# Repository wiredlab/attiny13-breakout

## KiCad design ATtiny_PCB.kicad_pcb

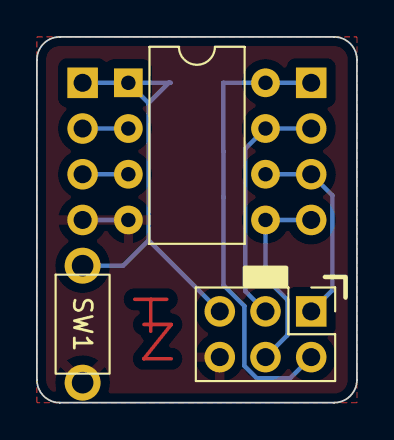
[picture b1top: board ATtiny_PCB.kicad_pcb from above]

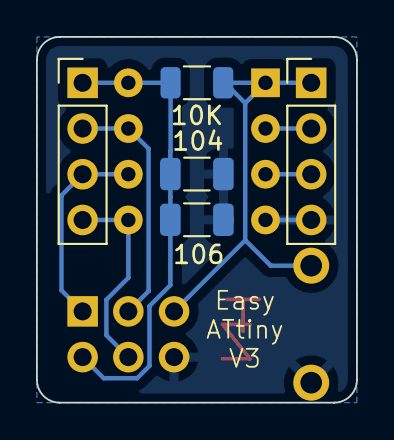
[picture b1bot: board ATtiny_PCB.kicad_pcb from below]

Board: 2 copper layers, 17.8 x 20.3 mm, 8 parts (5 on the bottom side), 8 nets.

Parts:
10K: R; R_1206_3216Metric
104, 106: C; C_1206_3216Metric
J1, J2: Conn_01x04; PinHeader_1x04_P2.54mm_Vertical
J3: Conn_02x03_Odd_Even; PinHeader_2x03_P2.54mm_Vertical
SW1: SW_Push; Push Button Switch Goldsun Electronics KRS-3550-BK-R
U1: ATtiny13-20P; DIP-8_W7.62mm

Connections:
ExtCLKI: J1.2, U1.2 (PB3)
GND: 104.2, 106.2, J1.4, J3.6, SW1.1, U1.4 (GND)
MISO: J2.3, J3.1, U1.6 (PB1)
MOSI: J2.4, J3.4, U1.5 (PB0)
PB4: J1.3, U1.3 (PB4)
Reset: 10K.1, J1.1, J3.5, SW1.2, U1.1 (~RESET/PB5)
SCK: J2.2, J3.3, U1.7 (PB2)
VCC: 10K.2, 104.1, 106.1, J2.1, J3.2, U1.8 (VCC)

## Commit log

2023-04-19 Add Timothy Ziemann version
2023-04-19 Original design
2023-04-19 Add gerbers from a previous fab run
2023-04-19 Ignore backup folder
